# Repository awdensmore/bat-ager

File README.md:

# bat-ager

This project is an automated hardware and software tool for aging batteries in a precise fashion. The repo includes both hardware schematics and firmware.

**HARDWARE**

The aging process is done by repeatedly charging and discharging the battery. The hardware therefore switches between a charging mode and a discharging mode. Charging is done using a bi-directional DC/DC converter powered by a benchtop supply. Discharging is done via a DC/DC converter, carefully controlling a fet that shorts the battery to ground. Current is measured using a shunt and op-amp. The PCB is divided into five charging sections so that multiple batteries may be aged simultaneously. The system is controlled using an STM32F0 MCU. Also supports injecting a small AC ripple voltage during charging and discharging, which is used to measure the battery's impedance in real time.

**FIRMWARE**

The firmware is based on the STM HAL libraries. Features include: 
+ Independent charge/discharge settings for each battery
+ Constant current / constant voltage charging, low-voltage disconnect
+ Programmable load for discharging
+ Injection of small AC ripple voltage
+ Data collection and reporting

~~The firmware is Arduino based to make development easy (though I use the [Arduino makefile](https://github.com/sudar/Arduino-Makefile) to make customizing and automation easier in Linux). Features will include:~~
~~+ Independent charge/discharge settings for each battery~~
~~+ Serial communication via FTDI cable. With a Raspberry Pi attached, can be monitored via SSH.~~
~~+ Safeties ?!~~

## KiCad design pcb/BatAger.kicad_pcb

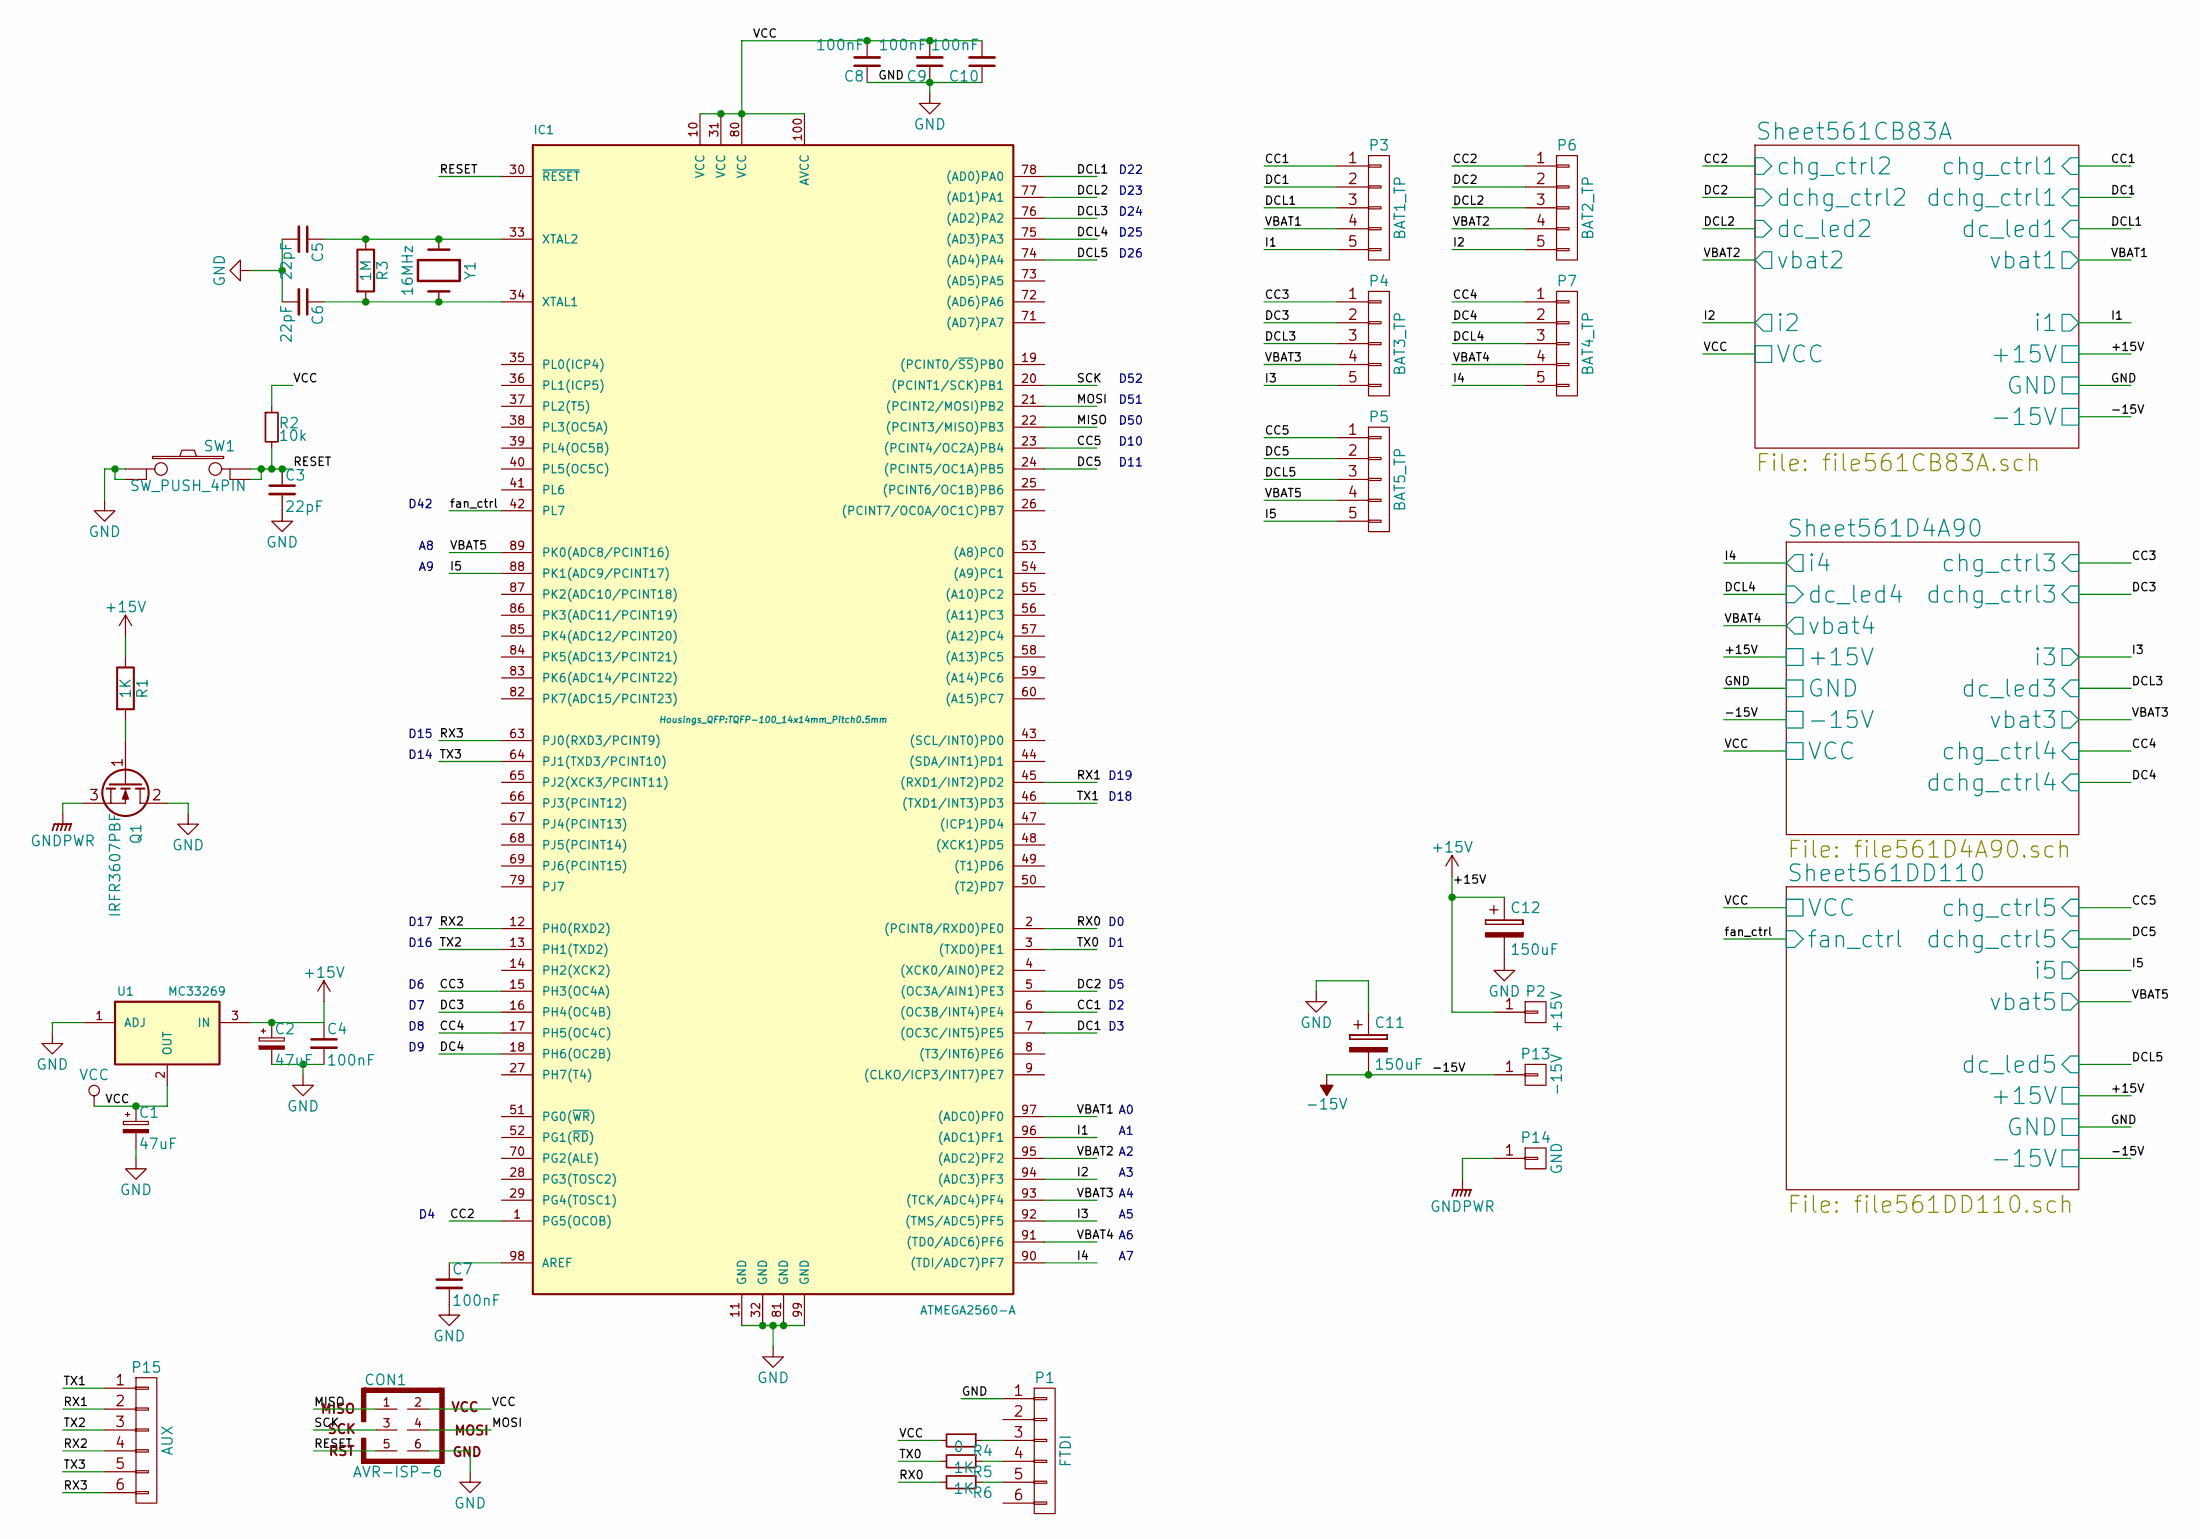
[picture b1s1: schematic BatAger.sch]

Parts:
C1, C2: 47uF; Elko_vert_11.2x6.3mm_RM2.5
C3, C5, C6: 22pF; C_0805_HandSoldering
C4, C7, C8, C9, C10: 100nF; C_0805_HandSoldering
C11, C12: 150uF; Elko_vert_11.5x8mm_RM3.5
CON1: AVR-ISP-6; Pin_Header_Straight_2x03
IC1: ATMEGA2560-A; TQFP-100_14x14mm_Pitch0.5mm
P1: FTDI; PINHEAD1-6
P2: +15V; Pin_Header_Straight_1x01
P3: BAT1_TP; Pin_Header_Straight_1x05
P4: BAT3_TP; Pin_Header_Straight_1x05
P5: BAT5_TP; Pin_Header_Straight_1x05
P6: BAT2_TP; Pin_Header_Straight_1x05
P7: BAT4_TP; Pin_Header_Straight_1x05
P13: -15V; Pin_Header_Straight_1x01
P14: GND; Pin_Header_Straight_1x01
P15: AUX; Pin_Header_Straight_1x06
Q1: IRFR3607PBF; TO-252-2Lead
R1, R5, R6: 1K; R_0805_HandSoldering
R2: 10k; R_0805_HandSoldering
R3: 1M; R_0805_HandSoldering
R4: 0; R_0805_HandSoldering
SW1: SW_PUSH_4PIN; SW_PUSH_4.5x6.5mm
U1: MC33269; TO-252-2Lead
Y1: 16MHz; Crystal_HC49-U_Vertical

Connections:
+15V: C2.1, C4.1, C12.1, P2.1, R1.1, U1.3 (IN); also elsewhere on the board
-15V: C11.2, P13.1; also elsewhere on the board
/MISO: CON1.1, IC1.22 ((PCINT3/MISO)PB3)
/MOSI: CON1.4, IC1.21 ((PCINT2/MOSI)PB2)
/RESET: C3.1, CON1.5, IC1.30 (~RESET), R2.2, SW1.2
/RX0: IC1.2 ((PCINT8/RXD0)PE0), R6.2
/RX1: IC1.45 ((RXD1/INT2)PD2), P15.2
/RX2: IC1.12 (PH0(RXD2)), P15.4
/RX3: IC1.63 (PJ0(RXD3/PCINT9)), P15.6
/SCK: CON1.3, IC1.20 ((PCINT1/SCK)PB1)
/Sheet561CB83A/chg_ctrl1: IC1.6 ((OC3B/INT4)PE4), P3.1; also elsewhere on the board
/Sheet561CB83A/chg_ctrl2: IC1.1 (PG5(OCOB)), P6.1; also elsewhere on the board
/Sheet561CB83A/dc_led1: IC1.78 ((AD0)PA0), P3.3; also elsewhere on the board
/Sheet561CB83A/dc_led2: IC1.77 ((AD1)PA1), P6.3; also elsewhere on the board
/Sheet561CB83A/dchg_ctrl1: IC1.7 ((OC3C/INT5)PE5), P3.2; also elsewhere on the board
/Sheet561CB83A/dchg_ctrl2: IC1.5 ((OC3A/AIN1)PE3), P6.2; also elsewhere on the board
/Sheet561CB83A/i1: IC1.96 ((ADC1)PF1), P3.5; also elsewhere on the board
/Sheet561CB83A/i2: IC1.94 ((ADC3)PF3), P6.5; also elsewhere on the board
/Sheet561CB83A/vbat1: IC1.97 ((ADC0)PF0), P3.4; also elsewhere on the board
/Sheet561CB83A/vbat2: IC1.95 ((ADC2)PF2), P6.4; also elsewhere on the board
/Sheet561D4A90/chg_ctrl3: IC1.15 (PH3(OC4A)), P4.1; also elsewhere on the board
/Sheet561D4A90/chg_ctrl4: IC1.17 (PH5(OC4C)), P7.1; also elsewhere on the board
/Sheet561D4A90/dc_led3: IC1.76 ((AD2)PA2), P4.3; also elsewhere on the board
/Sheet561D4A90/dc_led4: IC1.75 ((AD3)PA3), P7.3; also elsewhere on the board
/Sheet561D4A90/dchg_ctrl3: IC1.16 (PH4(OC4B)), P4.2; also elsewhere on the board
/Sheet561D4A90/dchg_ctrl4: IC1.18 (PH6(OC2B)), P7.2; also elsewhere on the board
/Sheet561D4A90/i3: IC1.92 ((TMS/ADC5)PF5), P4.5; also elsewhere on the board
/Sheet561D4A90/i4: IC1.90 ((TDI/ADC7)PF7), P7.5; also elsewhere on the board
/Sheet561D4A90/vbat3: IC1.93 ((TCK/ADC4)PF4), P4.4; also elsewhere on the board
/Sheet561D4A90/vbat4: IC1.91 ((TD0/ADC6)PF6), P7.4; also elsewhere on the board
/Sheet561DD110/chg_ctrl5: IC1.23 ((PCINT4/OC2A)PB4), P5.1; also elsewhere on the board
/Sheet561DD110/dc_led5: IC1.74 ((AD4)PA4), P5.3; also elsewhere on the board
/Sheet561DD110/dchg_ctrl5: IC1.24 ((PCINT5/OC1A)PB5), P5.2; also elsewhere on the board
/Sheet561DD110/fan_ctrl: IC1.42 (PL7); also elsewhere on the board
/Sheet561DD110/i5: IC1.88 (PK1(ADC9/PCINT17)), P5.5; also elsewhere on the board
/Sheet561DD110/vbat5: IC1.89 (PK0(ADC8/PCINT16)), P5.4; also elsewhere on the board
/TX0: IC1.3 ((TXD0)PE1), R5.2
/TX1: IC1.46 ((TXD1/INT3)PD3), P15.1
/TX2: IC1.13 (PH1(TXD2)), P15.3
/TX3: IC1.64 (PJ1(TXD3/PCINT10)), P15.5
GND: C1.2, C2.2, C3.2, C4.2, C5.2, C6.2, C7.2, C8.1, C9.1, C10.1, C11.1, C12.2, CON1.6, IC1.11 (GND), IC1.32 (GND), IC1.81 (GND), IC1.99 (GND), P1.1, Q1.2 (D), SW1.1, U1.1 (ADJ); also elsewhere on the board
GNDPWR: P14.1, Q1.3 (S)
unnamed: C5.1, IC1.33 (XTAL2), R3.1, Y1.1
unnamed: C6.1, IC1.34 (XTAL1), R3.2, Y1.2
unnamed: C7.1, IC1.98 (AREF)
unnamed: P1.3, R4.1
unnamed: P1.4, R5.1
unnamed: P1.5, R6.1
unnamed: Q1.1 (G), R1.2
VCC: C1.1, C8.2, C9.2, C10.2, CON1.2, IC1.10 (VCC), IC1.31 (VCC), IC1.80 (VCC), IC1.100 (AVCC), R2.1, R4.2, U1.2 (OUT); also elsewhere on the board

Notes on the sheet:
D22
D23
D24
D25
D10
D11
D26
D50
D51
D52
D18
D19
D16
D17
D14
D15
D42

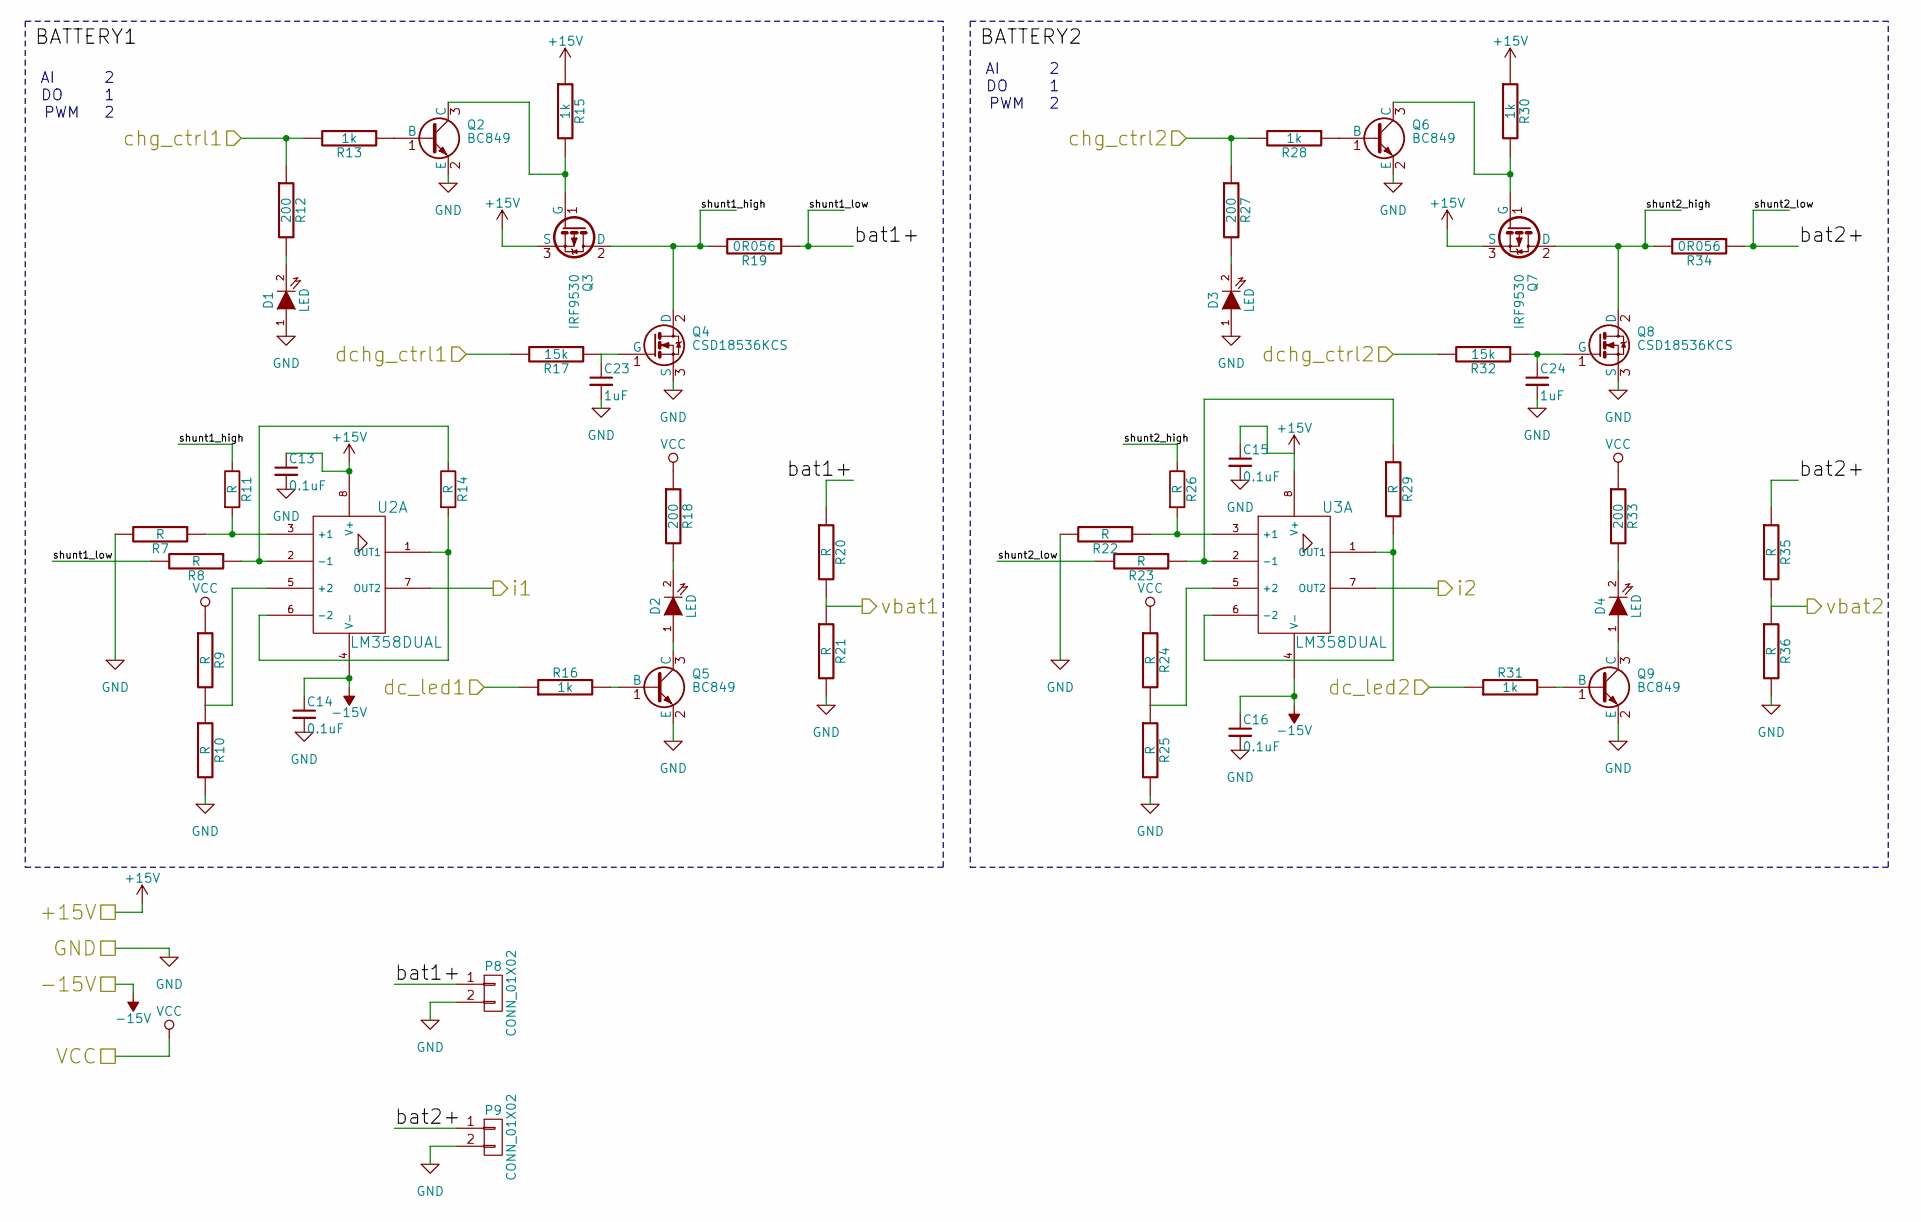
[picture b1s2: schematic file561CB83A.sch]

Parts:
C13, C14, C15, C16: 0.1uF; C_0805_HandSoldering
C23, C24: 1uF; C_0805_HandSoldering
D1, D2, D3, D4: LED; LED-0805
P8, P9: CONN_01X02; PINHEAD1-2_200mil
Q2, Q5, Q6, Q9: BC849; SOT-23_Handsoldering
Q3, Q7: IRF9530; TO-220
Q4, Q8: CSD18536KCS; TO-220
R7, R8, R9, R10, R11, R14, R20, R21, R22, R23, R24, R25, R26, R29, R35, R36: R; Resistor_Horizontal_RM10mm
R12, R18: 200; R_0805_HandSoldering; Part # RC0805JR-07 200R
R13, R16: 1k; R_0805_HandSoldering; Part # RC0805JR-07 200R
R15, R28, R30, R31: 1k; R_0805_HandSoldering
R17: 15k; R_0805_HandSoldering; Part # RC0805JR-07 200R
R19, R34: 0R056; R_2512_HandSoldering
R27, R33: 200; R_0805_HandSoldering
R32: 15k; R_0805_HandSoldering
U2, U3: LM358DUAL; SOIC-8_3.9x4.9mm_Pitch1.27mm

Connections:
+15V: C13.1, C15.1, Q3.3 (S), Q7.3 (S), R15.1, R30.1, U2.8 (V+), U3.8 (V+); also elsewhere on the board
-15V: C14.1, C16.1, U2.4 (V-), U3.4 (V-); also elsewhere on the board
/Sheet561CB83A/bat1+: P8.1, R8.2, R19.1, R20.1
/Sheet561CB83A/bat2+: P9.1, R23.2, R34.1, R35.1
/Sheet561CB83A/chg_ctrl1: R12.1, R13.2; also elsewhere on the board
/Sheet561CB83A/chg_ctrl2: R27.1, R28.2; also elsewhere on the board
/Sheet561CB83A/dc_led1: R16.1; also elsewhere on the board
/Sheet561CB83A/dc_led2: R31.1; also elsewhere on the board
/Sheet561CB83A/dchg_ctrl1: R17.2; also elsewhere on the board
/Sheet561CB83A/dchg_ctrl2: R32.2; also elsewhere on the board
/Sheet561CB83A/i1: U2.7 (OUT2); also elsewhere on the board
/Sheet561CB83A/i2: U3.7 (OUT2); also elsewhere on the board
/Sheet561CB83A/shunt1_high: Q3.2 (D), Q4.2 (D), R11.1, R19.2
/Sheet561CB83A/shunt2_high: Q7.2 (D), Q8.2 (D), R26.1, R34.2
/Sheet561CB83A/vbat1: R20.2, R21.1; also elsewhere on the board
/Sheet561CB83A/vbat2: R35.2, R36.1; also elsewhere on the board
GND: C13.2, C14.2, C15.2, C16.2, C23.2, C24.2, D1.1 (A), D3.1 (A), P8.2, P9.2, Q2.2 (E), Q4.3 (S), Q5.2 (E), Q6.2 (E), Q8.3 (S), Q9.2 (E), R7.2, R10.2, R21.2, R22.2, R25.2, R36.2; also elsewhere on the board
unnamed: C23.1, Q4.1 (G), R17.1
unnamed: C24.1, Q8.1 (G), R32.1
unnamed: D1.2 (K), R12.2
unnamed: D2.1 (A), Q5.3 (C)
unnamed: D2.2 (K), R18.2
unnamed: D3.2 (K), R27.2
unnamed: D4.1 (A), Q9.3 (C)
unnamed: D4.2 (K), R33.2
unnamed: Q2.1 (B), R13.1
unnamed: Q2.3 (C), Q3.1 (G), R15.2
unnamed: Q5.1 (B), R16.2
unnamed: Q6.1 (B), R28.1
unnamed: Q6.3 (C), Q7.1 (G), R30.2
unnamed: Q9.1 (B), R31.2
unnamed: R9.2, R10.1, U2.5 (+2)
unnamed: R7.1, R11.2, U2.3 (+1)
unnamed: R8.1, R14.1, U2.2 (-1)
unnamed: R14.2, U2.1 (OUT1), U2.6 (-2)
unnamed: R22.1, R26.2, U3.3 (+1)
unnamed: R23.1, R29.1, U3.2 (-1)
unnamed: R24.2, R25.1, U3.5 (+2)
unnamed: R29.2, U3.1 (OUT1), U3.6 (-2)
VCC: R9.1, R18.1, R24.1, R33.1; also elsewhere on the board

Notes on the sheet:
AI 2 DO 1 PWM 2

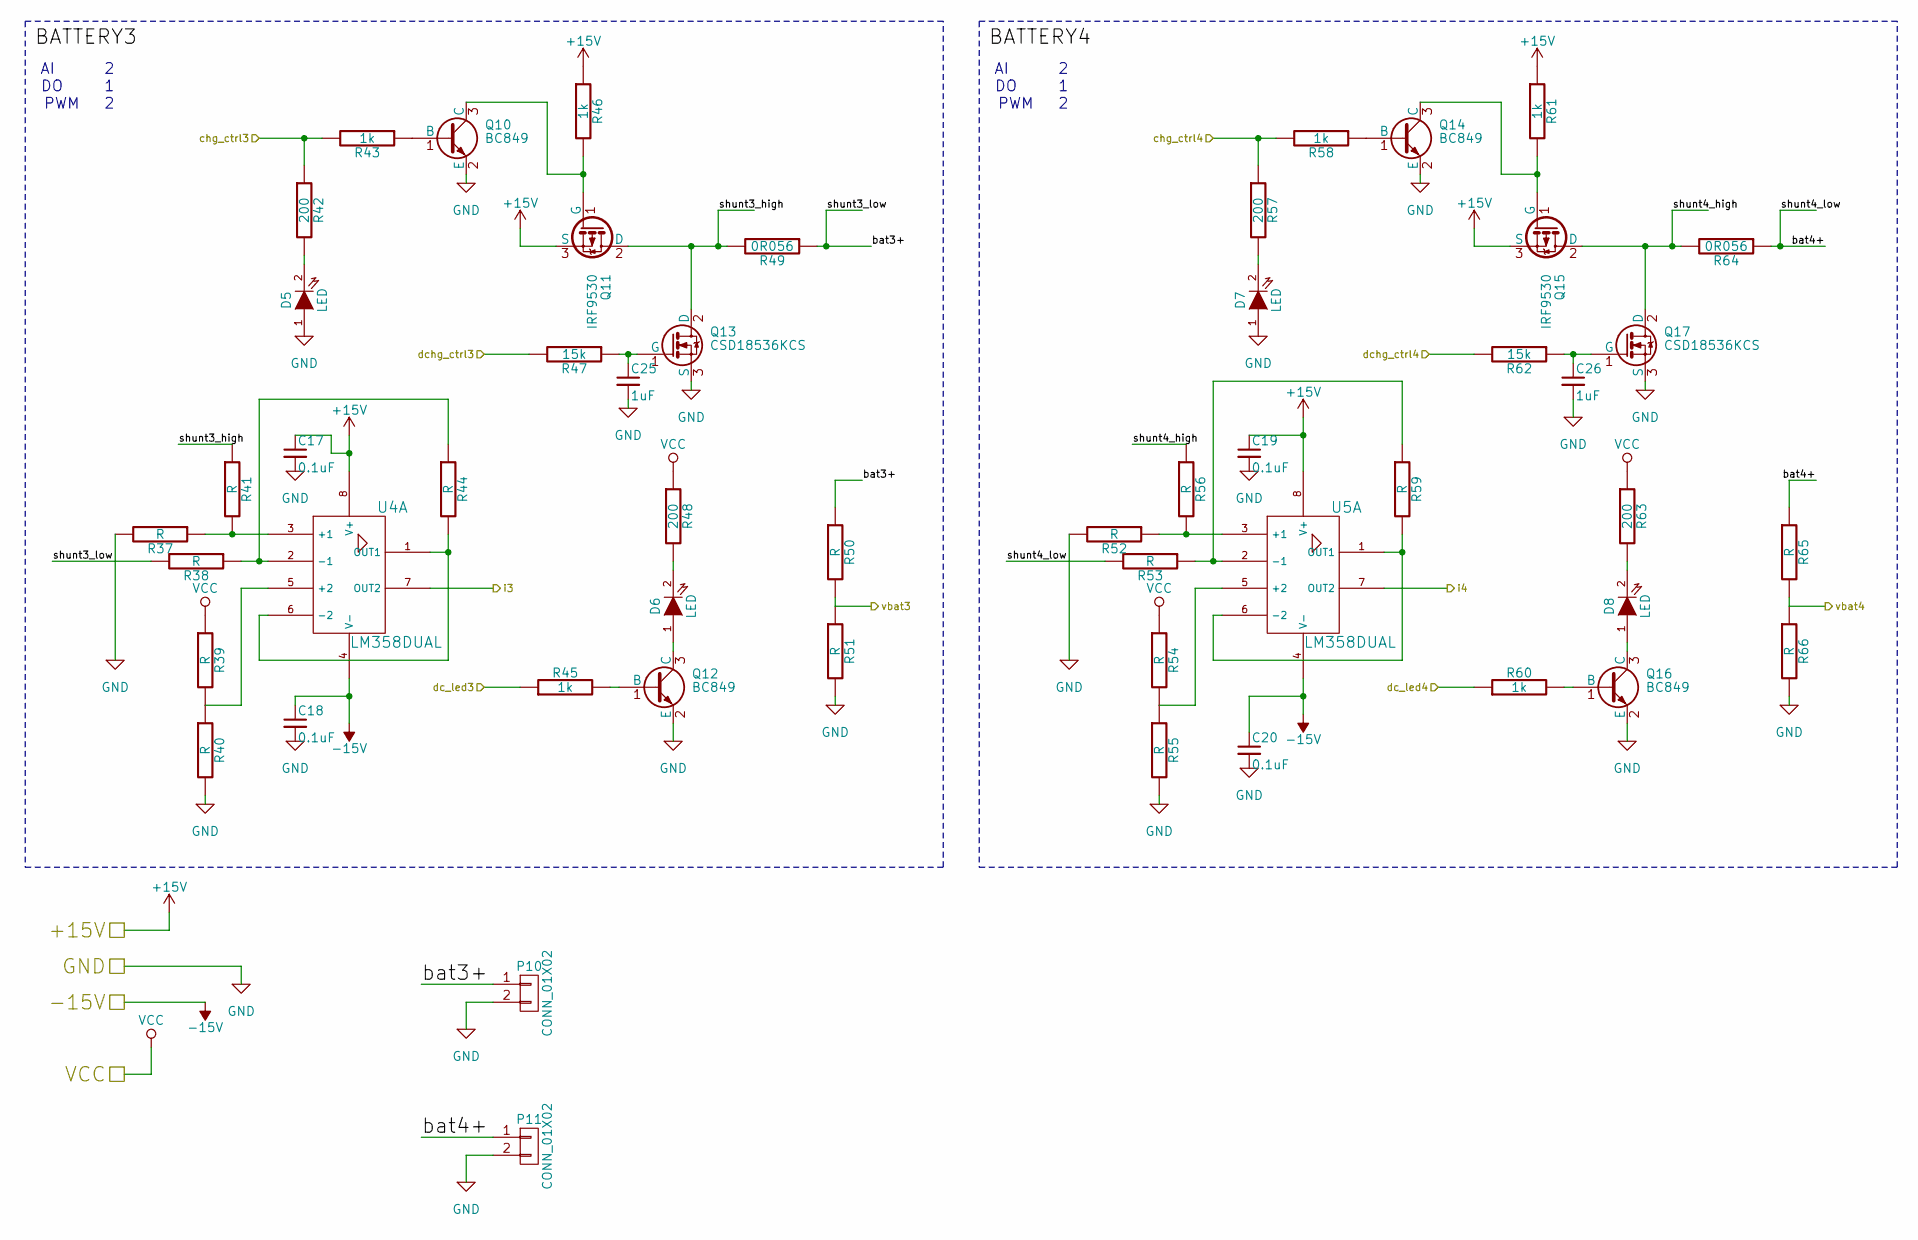
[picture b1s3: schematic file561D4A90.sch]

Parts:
C17, C18, C19, C20: 0.1uF; C_0805_HandSoldering
C25: 1uF; C_0805_HandSoldering
C26: 1uF; C_Disc_D3_P2.5
D5, D6, D7, D8: LED; LED-0805
P10, P11: CONN_01X02; PINHEAD1-2_200mil
Q10, Q12, Q14, Q16: BC849; SOT-23_Handsoldering
Q11, Q15: IRF9530; TO-220
Q13, Q17: CSD18536KCS; TO-220
R37, R38, R39, R40, R41, R44, R50, R51, R52, R53, R54, R55, R56, R59, R65, R66: R; Resistor_Horizontal_RM10mm
R42, R48, R57, R63: 200; R_0805_HandSoldering
R43, R45, R46, R58, R60, R61: 1k; R_0805_HandSoldering
R47: 15k; R_0805_HandSoldering
R49, R64: 0R056; R_2512_HandSoldering; Part # RL2512 FK-07 0R056
R62: 15k; Resistor_Horizontal_RM10mm
U4, U5: LM358DUAL; SOIC-8_3.9x4.9mm_Pitch1.27mm

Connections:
+15V: C17.1, C19.1, Q11.3 (S), Q15.3 (S), R46.1, R61.1, U4.8 (V+), U5.8 (V+); also elsewhere on the board
-15V: C18.1, C20.1, U4.4 (V-), U5.4 (V-); also elsewhere on the board
/Sheet561D4A90/bat3+: P10.1, R38.2, R49.1, R50.1
/Sheet561D4A90/bat4+: P11.1, R53.2, R64.1, R65.1
/Sheet561D4A90/chg_ctrl3: R42.1, R43.2; also elsewhere on the board
/Sheet561D4A90/chg_ctrl4: R57.1, R58.2; also elsewhere on the board
/Sheet561D4A90/dc_led3: R45.1; also elsewhere on the board
/Sheet561D4A90/dc_led4: R60.1; also elsewhere on the board
/Sheet561D4A90/dchg_ctrl3: R47.2; also elsewhere on the board
/Sheet561D4A90/dchg_ctrl4: R62.2; also elsewhere on the board
/Sheet561D4A90/i3: U4.7 (OUT2); also elsewhere on the board
/Sheet561D4A90/i4: U5.7 (OUT2); also elsewhere on the board
/Sheet561D4A90/shunt3_high: Q11.2 (D), Q13.2 (D), R41.1, R49.2
/Sheet561D4A90/shunt4_high: Q15.2 (D), Q17.2 (D), R56.1, R64.2
/Sheet561D4A90/vbat3: R50.2, R51.1; also elsewhere on the board
/Sheet561D4A90/vbat4: R65.2, R66.1; also elsewhere on the board
GND: C17.2, C18.2, C19.2, C20.2, C25.2, C26.2, D5.1 (A), D7.1 (A), P10.2, P11.2, Q10.2 (E), Q12.2 (E), Q13.3 (S), Q14.2 (E), Q16.2 (E), Q17.3 (S), R37.2, R40.2, R51.2, R52.2, R55.2, R66.2; also elsewhere on the board
unnamed: C25.1, Q13.1 (G), R47.1
unnamed: C26.1, Q17.1 (G), R62.1
unnamed: D5.2 (K), R42.2
unnamed: D6.1 (A), Q12.3 (C)
unnamed: D6.2 (K), R48.2
unnamed: D7.2 (K), R57.2
unnamed: D8.1 (A), Q16.3 (C)
unnamed: D8.2 (K), R63.2
unnamed: Q10.1 (B), R43.1
unnamed: Q10.3 (C), Q11.1 (G), R46.2
unnamed: Q12.1 (B), R45.2
unnamed: Q14.1 (B), R58.1
unnamed: Q14.3 (C), Q15.1 (G), R61.2
unnamed: Q16.1 (B), R60.2
unnamed: R37.1, R41.2, U4.3 (+1)
unnamed: R38.1, R44.1, U4.2 (-1)
unnamed: R39.2, R40.1, U4.5 (+2)
unnamed: R44.2, U4.1 (OUT1), U4.6 (-2)
unnamed: R52.1, R56.2, U5.3 (+1)
unnamed: R53.1, R59.1, U5.2 (-1)
unnamed: R54.2, R55.1, U5.5 (+2)
unnamed: R59.2, U5.1 (OUT1), U5.6 (-2)
VCC: R39.1, R48.1, R54.1, R63.1; also elsewhere on the board

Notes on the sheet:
AI 2 DO 1 PWM 2

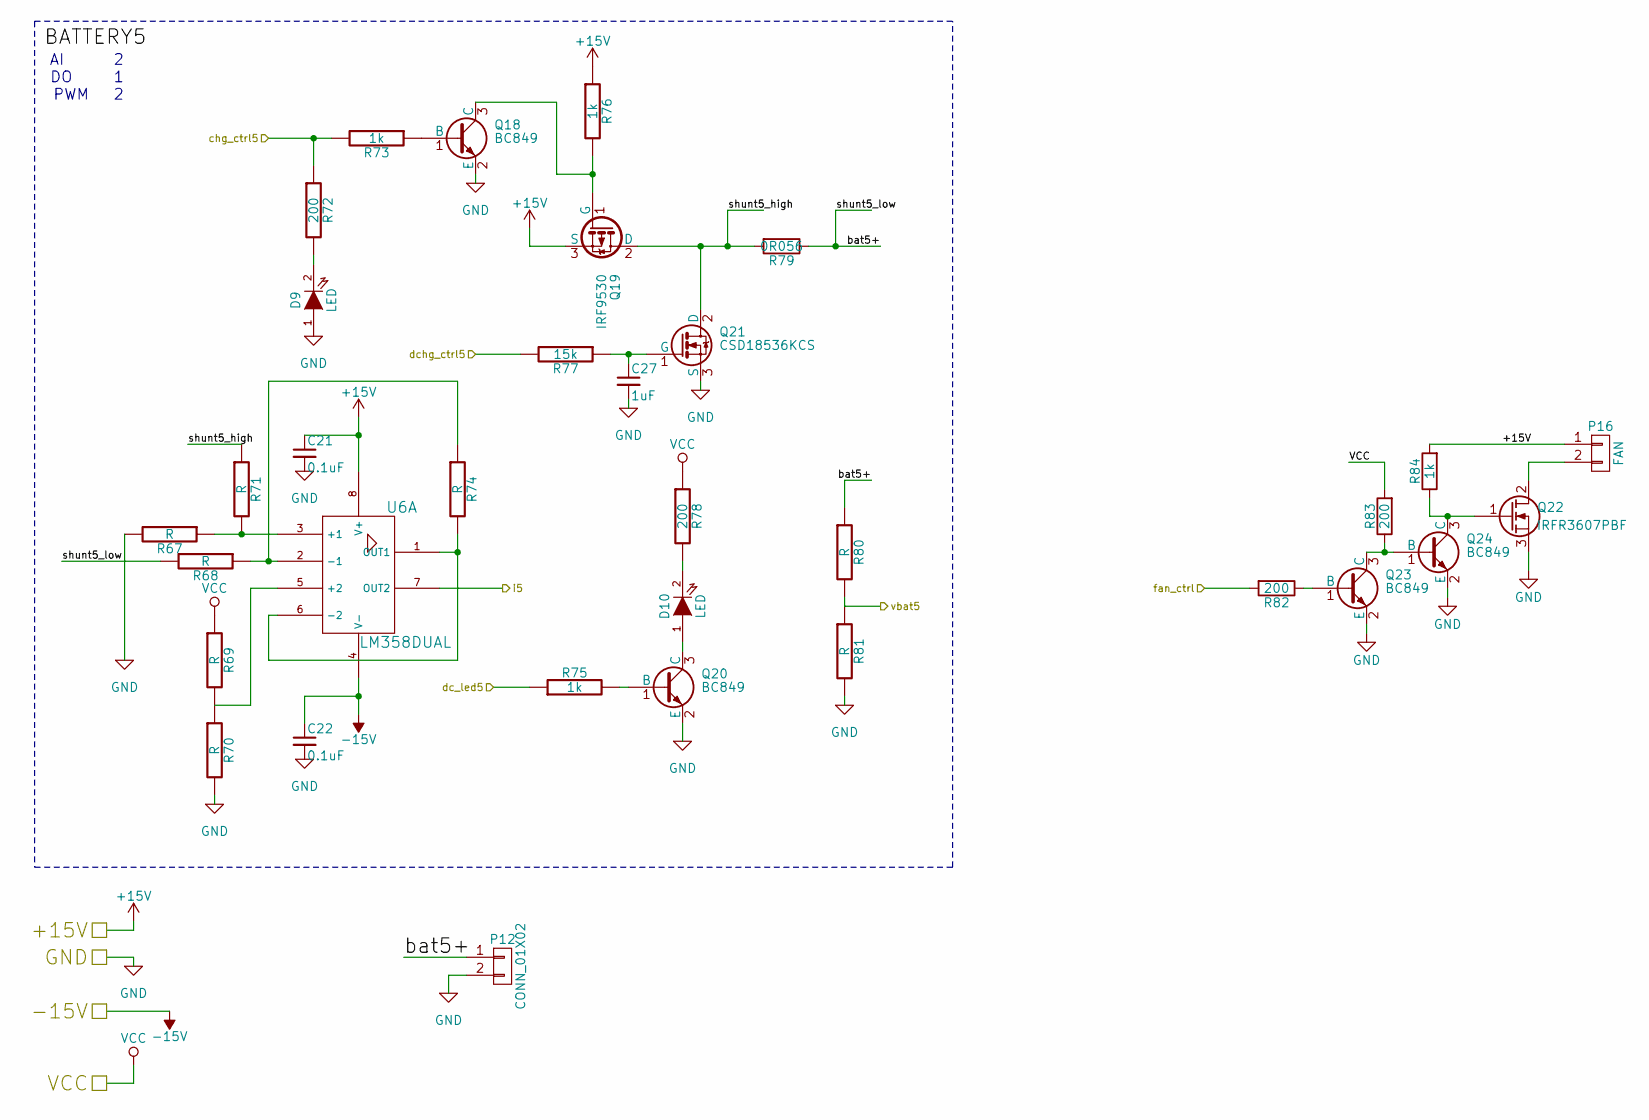
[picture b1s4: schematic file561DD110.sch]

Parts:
C21, C22: 0.1uF; C_0805_HandSoldering
C27: 1uF; C_0805_HandSoldering
D9, D10: LED; LED-0805
P12: CONN_01X02; PINHEAD1-2_200mil
P16: FAN; Pin_Header_Straight_1x02
Q18, Q20, Q23, Q24: BC849; SOT-23_Handsoldering
Q19: IRF9530; TO-220
Q21: CSD18536KCS; TO-220
Q22: IRFR3607PBF; TO-252-2Lead
R67, R68, R69, R70, R71, R74, R80, R81: R; Resistor_Horizontal_RM10mm
R72, R78, R82, R83: 200; R_0805_HandSoldering
R73, R75, R76, R84: 1k; R_0805_HandSoldering
R77: 15k; R_0805_HandSoldering
R79: 0R056; R_2512_HandSoldering; Part # RL2512 FK-07 0R056
U6: LM358DUAL; SOIC-8_3.9x4.9mm_Pitch1.27mm

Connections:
+15V: C21.1, P16.1, Q19.3 (S), R76.1, R84.2, U6.8 (V+); also elsewhere on the board
-15V: C22.1, U6.4 (V-); also elsewhere on the board
/Sheet561DD110/bat5+: P12.1, R68.2, R79.1, R80.1
/Sheet561DD110/chg_ctrl5: R72.1, R73.2; also elsewhere on the board
/Sheet561DD110/dc_led5: R75.1; also elsewhere on the board
/Sheet561DD110/dchg_ctrl5: R77.2; also elsewhere on the board
/Sheet561DD110/fan_ctrl: R82.2; also elsewhere on the board
/Sheet561DD110/i5: U6.7 (OUT2); also elsewhere on the board
/Sheet561DD110/shunt5_high: Q19.2 (D), Q21.2 (D), R71.1, R79.2
/Sheet561DD110/vbat5: R80.2, R81.1; also elsewhere on the board
GND: C21.2, C22.2, C27.2, D9.1 (A), P12.2, Q18.2 (E), Q20.2 (E), Q21.3 (S), Q22.3 (S), Q23.2 (E), Q24.2 (E), R67.2, R70.2, R81.2; also elsewhere on the board
unnamed: C27.1, Q21.1 (G), R77.1
unnamed: D9.2 (K), R72.2
unnamed: D10.1 (A), Q20.3 (C)
unnamed: D10.2 (K), R78.2
unnamed: P16.2, Q22.2 (D)
unnamed: Q18.1 (B), R73.1
unnamed: Q18.3 (C), Q19.1 (G), R76.2
unnamed: Q20.1 (B), R75.2
unnamed: Q22.1 (G), Q24.3 (C), R84.1
unnamed: Q23.1 (B), R82.1
unnamed: Q23.3 (C), Q24.1 (B), R83.1
unnamed: R67.1, R71.2, U6.3 (+1)
unnamed: R68.1, R74.1, U6.2 (-1)
unnamed: R69.2, R70.1, U6.5 (+2)
unnamed: R74.2, U6.1 (OUT1), U6.6 (-2)
VCC: R69.1, R78.1, R83.2; also elsewhere on the board

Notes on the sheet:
AI 2 DO 1 PWM 2

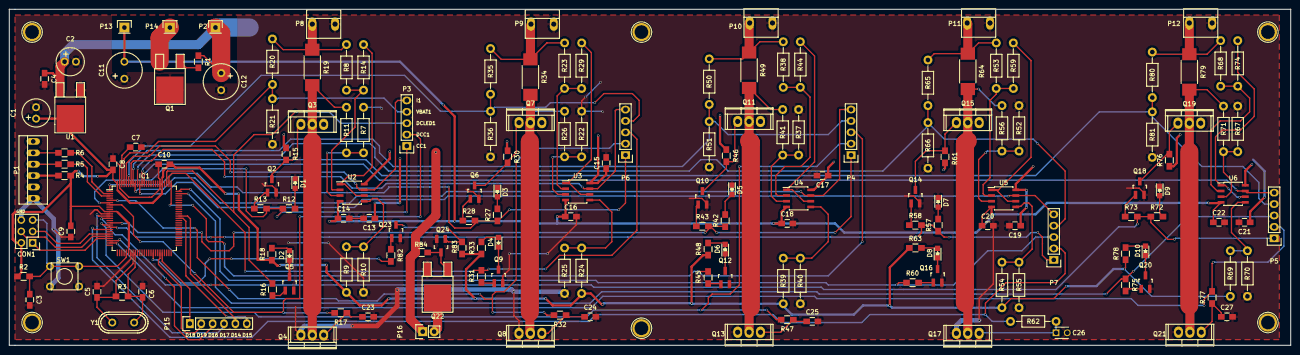
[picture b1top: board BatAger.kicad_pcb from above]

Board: 2 copper layers, 285.8 x 74.9 mm, 171 parts (0 on the bottom side), 119 nets.

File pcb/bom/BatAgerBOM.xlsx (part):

Bill of Materials
PCB: | Battery Ager |  |  |  | Per Unit Cost | 397.53066666666723
 |  |  |  |  | Quantity | 2
 |  |  |  |  | Components | 795.06133333333446
 |  |  |  |  | VAT @ 14% | 111.30858666666684
 |  |  |  |  | Total | 906.36992000000134
Reference | Type | Value | Package | Manufacturer | Part # | Price (ZAR) | Link | Notes
C1 | Cap | 47uF | PTH 11.2x6.3mm | Suntan | TS13D CD110X 47UF35V | 1.24 | http://www.mantech.co.za/ProductInfo.aspx?Item=72M3151
C10 | Cap | 0.1uF | 0805 | Yageo | C0805ZRY5V9BB104 | 0.28000000000000003 | http://www.mantech.co.za/ProductInfo.aspx?Item=20M0861
C11 | Cap | 150uF | PTH 11.5x8mm | Rubycon | 35YXG150M 8x11.5 | 3 | http://www.mantech.co.za/ProductInfo.aspx?Item=72M4430
C12 | Cap | 150uF | PTH 11.5x8mm | Rubycon | 35YXG150M 8x11.5 | 3 | http://www.mantech.co.za/ProductInfo.aspx?Item=72M4431
C13 | Cap | 0.1uF | 0805 | Yageo | C0805ZRY5V9BB104 | 0.28000000000000003 | http://www.mantech.co.za/ProductInfo.aspx?Item=20M0861
C14 | Cap | 0.1uF | 0805 | Yageo | C0805ZRY5V9BB104 | 0.28000000000000003 | http://www.mantech.co.za/ProductInfo.aspx?Item=20M0861
C15 | Cap | 0.1uF | 0805 | Yageo | C0805ZRY5V9BB104 | 0.28000000000000003 | http://www.mantech.co.za/ProductInfo.aspx?Item=20M0861
C16 | Cap | 0.1uF | 0805 | Yageo | C0805ZRY5V9BB104 | 0.28000000000000003 | http://www.mantech.co.za/ProductInfo.aspx?Item=20M0861
C17 | Cap | 0.1uF | 0805 | Yageo | C0805ZRY5V9BB104 | 0.28000000000000003 | http://www.mantech.co.za/ProductInfo.aspx?Item=20M0861
C18 | Cap | 0.1uF | 0805 | Yageo | C0805ZRY5V9BB104 | 0.28000000000000003 | http://www.mantech.co.za/ProductInfo.aspx?Item=20M0861
C19 | Cap | 0.1uF | 0805 | Yageo | C0805ZRY5V9BB104 | 0.28000000000000003 | http://www.mantech.co.za/ProductInfo.aspx?Item=20M0861
C2 | Cap | 47uF | PTH 11.2x6.3mm | Suntan | TS13D CD110X 47UF35V | 1.24 | http://www.mantech.co.za/ProductInfo.aspx?Item=72M3152
C20 | Cap | 0.1uF | 0805 | Yageo | C0805ZRY5V9BB104 | 0.28000000000000003 | http://www.mantech.co.za/ProductInfo.aspx?Item=20M0861
C21 | Cap | 0.1uF | 0805 | Yageo | C0805ZRY5V9BB104 | 0.28000000000000003 | http://www.mantech.co.za/ProductInfo.aspx?Item=20M0861
C22 | Cap | 0.1uF | 0805 | Yageo | C0805ZRY5V9BB104 | 0.28000000000000003 | http://www.mantech.co.za/ProductInfo.aspx?Item=20M0861
C3 | Cap | 22pF | 0805 | Yageo | 0805CG221J500NT | 0.08 | http://www.mantech.co.za/ProductInfo.aspx?Item=35M3075
C4 | Cap | 0.1uF | 0805 | Yageo | C0805ZRY5V9BB104 | 0.28000000000000003 | http://www.mantech.co.za/ProductInfo.aspx?Item=35M1227
C5 | Cap | 22pF | 0805 | Yageo | 0805CG221J500NT | 0.08 | http://www.mantech.co.za/ProductInfo.aspx?Item=35M3075
C6 | Cap | 22pF | 0805 | Yageo | 0805CG221J500NT | 0.08 | http://www.mantech.co.za/ProductInfo.aspx?Item=35M3075
C7 | Cap | 0.1uF | 0805 | Yageo | C0805ZRY5V9BB104 | 0.28000000000000003 | http://www.mantech.co.za/ProductInfo.aspx?Item=20M0861
C8 | Cap | 0.1uF | 0805 | Yageo | C0805ZRY5V9BB104 | 0.28000000000000003 | http://www.mantech.co.za/ProductInfo.aspx?Item=20M0861
C9 | Cap | 0.1uF | 0805 | Yageo | C0805ZRY5V9BB104 | 0.28000000000000003 | http://www.mantech.co.za/ProductInfo.aspx?Item=20M0861
CON1 | Connector | ISP | PTH 2x3 100mil pitch |  |  |  |  | On hand
D1 | LED | Green | 0805 | Bright LED | BL-HX135A-TRB | 0.96 | http://www.mantech.co.za/ProductInfo.aspx?Item=12M0187
D10 | LED | Red | 0805 | Lite-On | LTST-C170EKT | 0.63 | http://www.mantech.co.za/ProductInfo.aspx?Item=35M5825
D2 | LED | Red | 0805 | Lite-On | LTST-C170EKT | 0.63 | http://www.mantech.co.za/ProductInfo.aspx?Item=35M5825
D3 | LED | Green | 0805 | Bright LED | BL-HX135A-TRB | 0.96 | http://www.mantech.co.za/ProductInfo.aspx?Item=12M0187
D4 | LED | Red | 0805 | Lite-On | LTST-C170EKT | 0.63 | http://www.mantech.co.za/ProductInfo.aspx?Item=35M5825
D5 | LED | Green | 0805 | Bright LED | BL-HX135A-TRB | 0.96 | http://www.mantech.co.za/ProductInfo.aspx?Item=12M0187
D6 | LED | Red | 0805 | Lite-On | LTST-C170EKT | 0.63 | http://www.mantech.co.za/ProductInfo.aspx?Item=35M5825
D7 | LED | Green | 0805 | Bright LED | BL-HX135A-TRB | 0.96 | http://www.mantech.co.za/ProductInfo.aspx?Item=12M0187
D8 | LED | Red | 0805 | Lite-On | LTST-C170EKT | 0.63 | http://www.mantech.co.za/ProductInfo.aspx?Item=35M5825
D9 | LED | Green | 0805 | Bright LED | BL-HX135A-TRB | 0.96 | http://www.mantech.co.za/ProductInfo.aspx?Item=12M0187
IC1 | MCU | 2560 | TQFP100 0.5mm pitch | Atmel | ATMEGA2560 | 270.97066666666666 | Farnell UK | 11 pounds shipping from UK (phone estimate). Qty 4 sample on order directly fro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
P1 | Header | FTDI | PTH 1x6 100mil pitch |  |  |  |  | On hand
P10 | Header | BAT3 TERM | PTH 1x2 150mil pitch |  |  |  |  | On hand
P11 | Header | BAT4 TERM | PTH 1x2 150mil pitch |  |  |  |  | On hand
P12 | Header | BAT5 TERM | PTH 1x2 150mil pitch |  |  |  |  | On hand
P13 | Header | -15V | PTH 1 |  |  |  |  | On hand
P14 | Header | GND | PTH 1 |  |  |  |  | On hand
P15 | Header | AUX | PTH 1x6 100mil pitch |  |  |  |  | On hand
P16 | Header | Fan | PTH 1x2 150mil pitch |  |  |  |  | On hand
P2 | Header | +15V | PTH 1 |  |  |  |  | On hand
P3 | Header | BAT1 TP | PTH 1x5 100mil pitch |  |  |  |  | On hand
P4 | Header | BAT2 TP | PTH 1x5 100mil pitch |  |  |  |  | On hand
P5 | Header | BAT3 TP | PTH 1x5 100mil pitch |  |  |  |  | On hand
P6 | Header | BAT4 TP | PTH 1x5 100mil pitch |  |  |  |  | On hand
P7 | Header | BAT5 TP | PTH 1x5 100mil pitch |  |  |  |  | On hand
P8 | Header | BAT1 TERM | PTH 1x2 150mil pitch |  |  |  |  | On hand
P9 | Header | BAT2 TERM | PTH 1x2 150mil pitch |  |  |  |  | On hand
Q01 | T / FET | NFET | TO252 | IR | IRFR3607PBF | 9.7799999999999994 | http://www.mantech.co.za/ProductInfo.aspx?Item=13M1648
Q02 | T / FET | Sgnl Trans | SOT23 | NXP | BC849B | 0.35 | http://www.mantech.co.za/ProductInfo.aspx?Item=35M3304
Q03 | T / FET | PFET | TO220 | IR | IRF9530N PBF | 7.05 | http://www.mantech.co.za/ProductInfo.aspx?Item=35M4416
Q04 | T / FET | NFET | TO220 | TI | CSD18536KCS | 0 | http://www.ti.com/product/csd18536kcs | On hand. Alternate part # AUIRL1404Z (IR) available from Farnell.
Q05 | T / FET | Sgnl Trans | SOT23 | NXP | BC849B | 0.35 | http://www.mantech.co.za/ProductInfo.aspx?Item=35M3304
Q06 | T / FET | Sgnl Trans | SOT23 | NXP | BC849B | 0.35 | http://www.mantech.co.za/ProductInfo.aspx?Item=35M3304
Q07 | T / FET | PFET | TO220 | IR | IRF9530N PBF | 7.05 | http://www.mantech.co.za/ProductInfo.aspx?Item=35M4416
Q08 | T / FET | NFET | TO220 | TI | CSD18536KCS | 0 | http://www.ti.com/product/csd18536kcs | On hand. Alternate part # AUIRL1404Z (IR) available from Farnell.
Q09 | T / FET | Sgnl Trans | SOT23 | NXP | BC849B | 0.35 | http://www.mantech.co.za/ProductInfo.aspx?Item=35M3304
Q10 | T / FET | Sgnl Trans | SOT23 | NXP | BC849B | 0.35 | http://www.mantech.co.za/ProductInfo.aspx?Item=35M3304
Q11 | T / FET | PFET | TO220 | IR | IRF9530N PBF | 7.05 | http://www.mantech.co.za/ProductInfo.aspx?Item=35M4416
Q12 | T / FET | Sgnl Trans | SOT23 | NXP | BC849B | 0.35 | http://www.mantech.co.za/ProductInfo.aspx?Item=35M3304
Q13 | T / FET | NFET | TO220 | TI | CSD18536KCS | 0 | http://www.ti.com/product/csd18536kcs | On hand. Alternate part # AUIRL1404Z (IR) available from Farnell.
Q14 | T / FET | Sgnl Trans | SOT23 | NXP | BC849B | 0.35 | http://www.mantech.co.za/ProductInfo.aspx?Item=35M3304
Q15 | T / FET | PFET | TO220 | IR | IRF9530N PBF | 7.05 | http://www.mantech.co.za/ProductInfo.aspx?Item=35M4416
Q16 | T / FET | Sgnl Trans | SOT23 | NXP | BC849B | 0.35 | http://www.mantech.co.za/ProductInfo.aspx?Item=35M3304
Q17 | T / FET | NFET | TO220 | TI | CSD18536KCS | 0 | http://www.ti.com/product/csd18536kcs | On hand. Alternate part # AUIRL1404Z (IR) available from Farnell.
Q18 | T / FET | Sgnl Trans | SOT23 | NXP | BC849B | 0.35 | http://www.mantech.co.za/ProductInfo.aspx?Item=35M3304
Q19 | T / FET | PFET | TO220 | IR | IRF9530N PBF | 7.05 | http://www.mantech.co.za/ProductInfo.aspx?Item=35M4416
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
